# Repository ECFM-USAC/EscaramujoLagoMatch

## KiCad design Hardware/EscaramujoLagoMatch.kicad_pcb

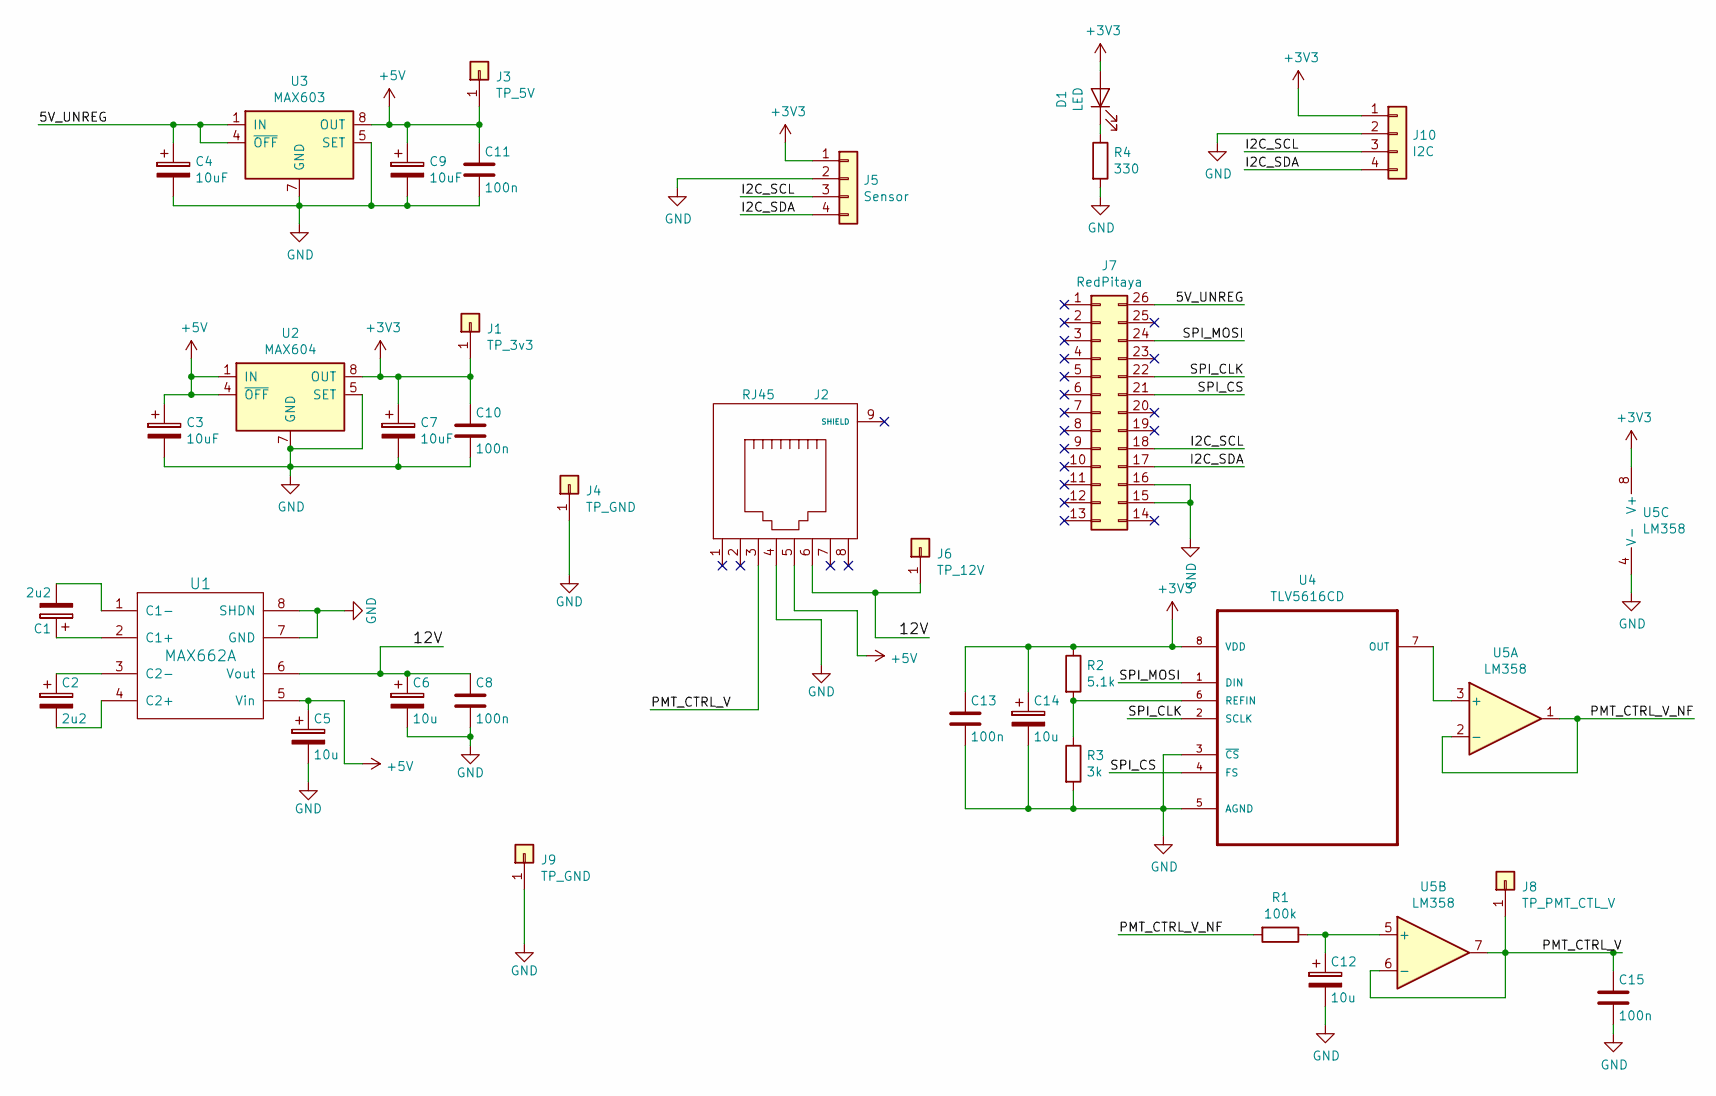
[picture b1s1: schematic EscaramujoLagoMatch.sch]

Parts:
C1, C2: 2u2; C_Disc_D5.0mm_W2.5mm_P2.50mm
C3, C4, C7, C9: 10uF; C_Disc_D5.0mm_W2.5mm_P2.50mm
C5, C6, C12, C14: 10u; C_Disc_D5.0mm_W2.5mm_P2.50mm
C8, C10, C11, C13, C15: 100n; C_0805_2012Metric_Pad1.15x1.40mm_HandSolder
D1: LED; LED_D5.0mm
J1: TP_3v3; PinHeader_1x01_P2.54mm_Vertical
J2: RJ45; RJ45_Amphenol_54602-x08_Horizontal
J3: TP_5V; PinHeader_1x01_P2.54mm_Vertical
J4, J9: TP_GND; PinHeader_1x01_P2.54mm_Vertical
J5: Sensor; PinHeader_1x04_P2.54mm_Vertical
J6: TP_12V; PinHeader_1x01_P2.54mm_Vertical
J7: RedPitaya; PinHeader_2x13_P2.54mm_Vertical
J8: TP_PMT_CTL_V; PinHeader_1x01_P2.54mm_Vertical
J10: I2C; PinHeader_1x04_P2.54mm_Vertical
R1: 100k; R_0805_2012Metric_Pad1.15x1.40mm_HandSolder
R2: 5.1k; R_Axial_DIN0207_L6.3mm_D2.5mm_P10.16mm_Horizontal
R3: 3k; R_Axial_DIN0207_L6.3mm_D2.5mm_P10.16mm_Horizontal
R4: 330; R_Axial_DIN0207_L6.3mm_D2.5mm_P10.16mm_Horizontal
U1: MAX662A; DIP-8_W7.62mm_Socket
U2: MAX604; DIP-8_W7.62mm_Socket
U3: MAX603; DIP-8_W7.62mm_Socket
U4: TLV5616CD
U5: LM358; DIP-8_W7.62mm_Socket

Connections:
+3V3: C7.1, C10.1, C13.1, C14.1, D1.2 (A), J1.1, J5.1, J10.1, R2.1, U2.8 (OUT), U4.8 (VDD), U5.8 (V+)
+5V: C3.1, C5.1, C9.1, C11.1, J2.5, J3.1, U1.5 (Vin), U2.1 (IN), U2.4 (~OFF), U3.8 (OUT)
/5V_UNREG: C4.1, J7.26, U3.1 (IN), U3.4 (~OFF)
/12V: C6.1, C8.1, J2.6, J6.1, U1.6 (Vout)
/I2C_SCL: J5.3, J7.18, J10.3
/I2C_SDA: J5.4, J7.17, J10.4
/PMT_CTRL_V: C15.1, J2.3, J8.1, U5.6 (-), U5.7
/PMT_CTRL_V_NF: R1.2, U5.1, U5.2 (-)
/SPI_CLK: J7.22, U4.2 (SCLK)
/SPI_CS: J7.21, U4.4 (FS)
/SPI_MOSI: J7.24, U4.1 (DIN)
GND: C3.2, C4.2, C5.2, C6.2, C7.2, C8.2, C9.2, C10.2, C11.2, C12.2, C13.2, C14.2, C15.2, J2.4, J4.1, J5.2, J7.15, J7.16, J9.1, J10.2, R3.2, R4.2, U1.7 (GND), U1.8 (SHDN), U2.2 (GND), U2.3 (GND), U2.5 (SET), U2.6 (GND), U2.7 (GND), U3.2 (GND), U3.3 (GND), U3.5 (SET), U3.6 (GND), U3.7 (GND), U4.3 (~CS), U4.5 (AGND), U5.4 (V-)
unnamed: C1.1, U1.2 (C1+)
unnamed: C1.2, U1.1 (C1-)
unnamed: C2.1, U1.3 (C2-)
unnamed: C2.2, U1.4 (C2+)
unnamed: C12.1, R1.1, U5.5 (+)
unnamed: D1.1 (K), R4.1
unnamed: R2.2, R3.1, U4.6 (REFIN)
unnamed: U4.7 (OUT), U5.3 (+)

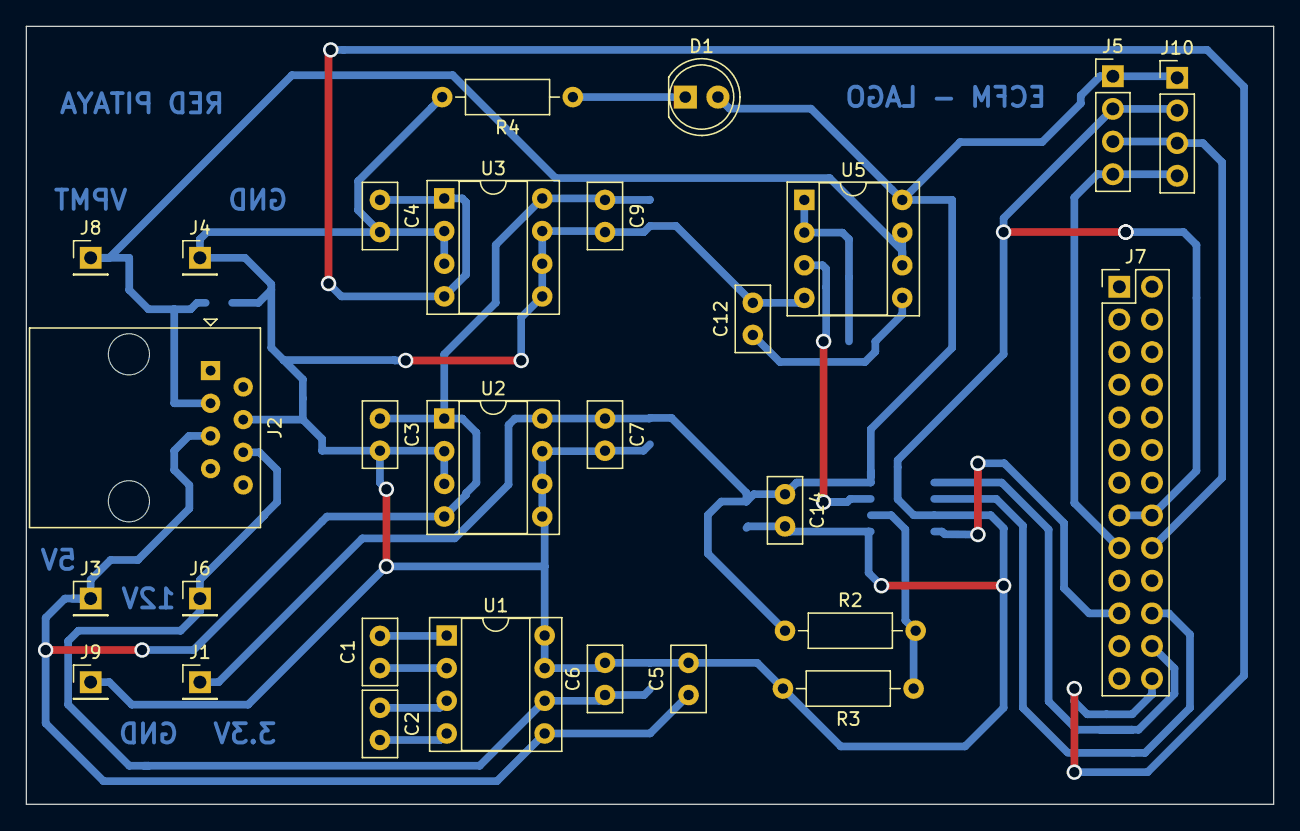
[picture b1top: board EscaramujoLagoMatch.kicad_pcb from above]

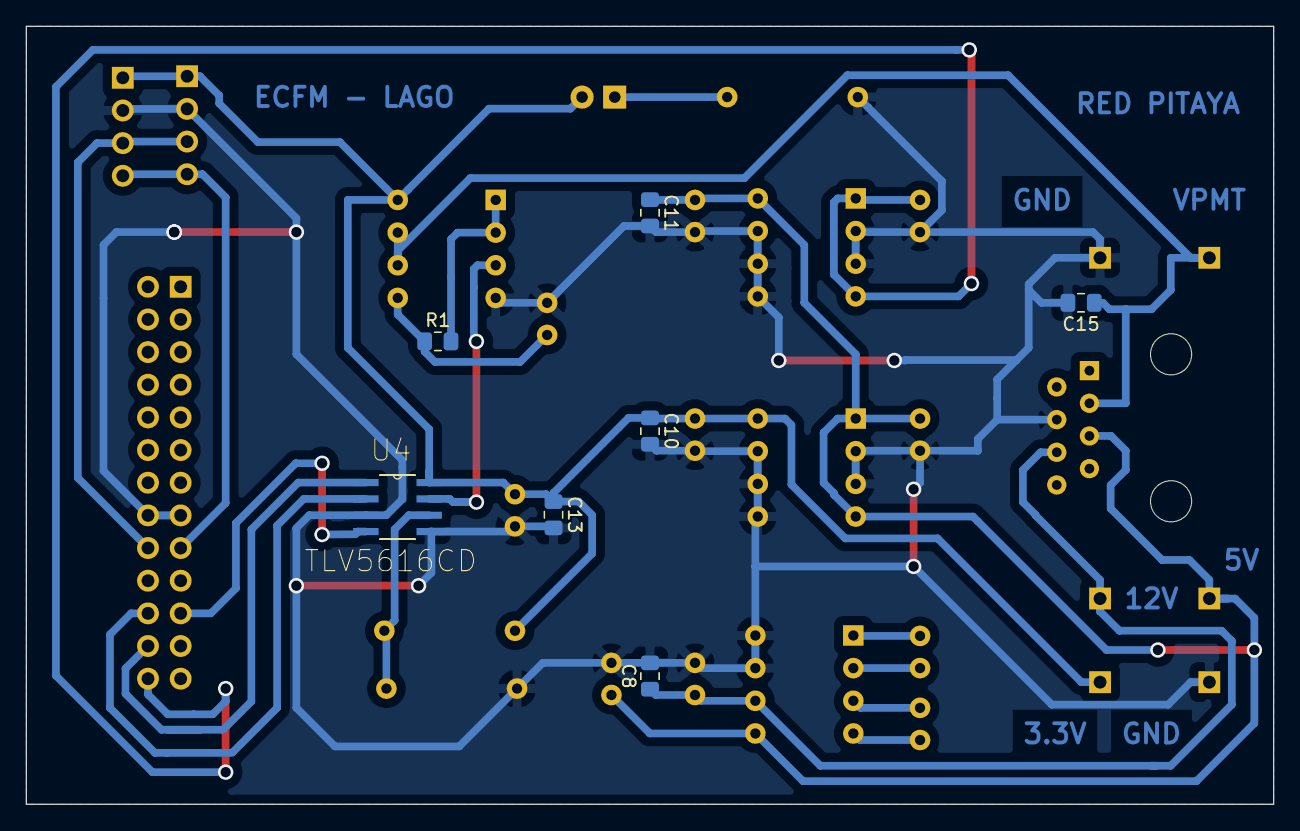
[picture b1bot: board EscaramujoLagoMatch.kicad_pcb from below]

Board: 2 copper layers, 97.0 x 60.5 mm, 35 parts (7 on the bottom side), 20 nets.

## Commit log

2016-09-09 :lollipop: Added .gitattributes & .gitignore files
2016-09-13 Preliminary library components added KiCAD
2016-10-28 PCB Design Done
    Includes custom library files
2016-11-07 Final printable PCB design
2019-03-05 Updated footprints
2019-03-07 PCB Finished
